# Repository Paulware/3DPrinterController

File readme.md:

3D Printer Controller

Parts
  $4 HBridge: 
  <br>
  [Get $4 HBridge on ebay](http://www.ebay.com/itm/L298N-DC-Stepper-Motor-Dual-H-Bridge-Drive-Controller-Board-Module-for-Arduino-/380520063503?)
  
Online videos:
  [Prototype](http://www.youtube.com/watch?v=m45CU5rBINc)    

Project Status
* Initial Creation 2/18/2013
* Ordered Updated board from Iteadstudio 2/22/2013
  
Questions/Comments
  paulware@hotmail.com
  
Help with projects
  [I help on Fiverr](http://fiverr.com/paulware/help-with-your-arduino-project)

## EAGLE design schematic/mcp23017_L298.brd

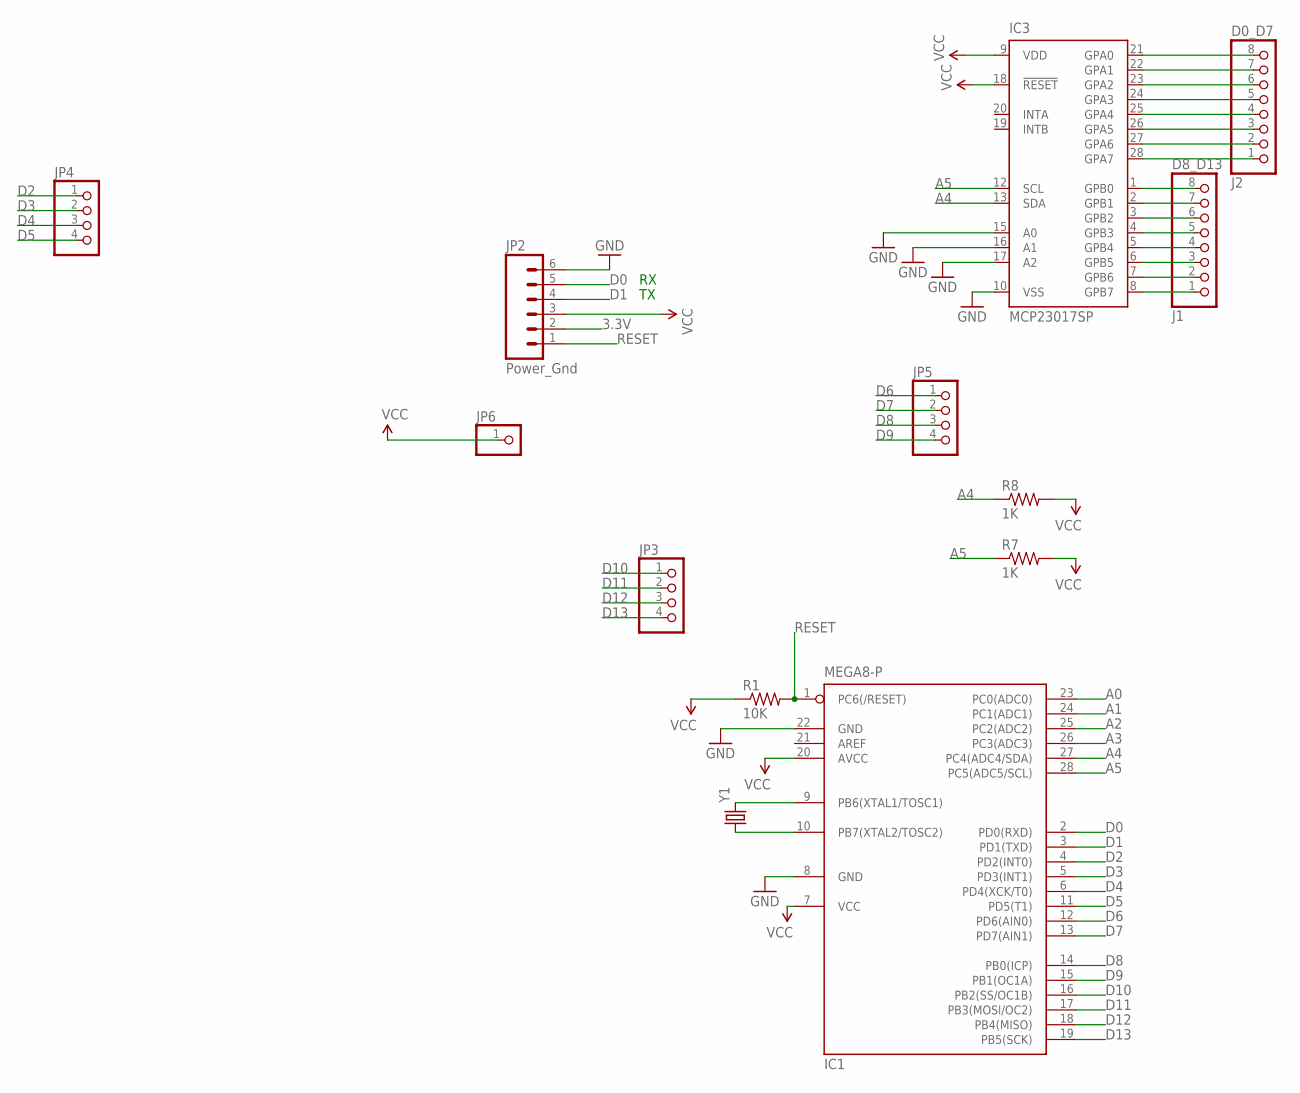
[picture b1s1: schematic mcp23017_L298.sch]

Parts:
IC1: MEGA8-P; DIL28-3
IC3: MCP23017SP; DIL28-3
J1: D8_D13; 1X08
J2: D0_D7; 1X08
JP2: Power_Gnd; 1X06
JP3, JP4, JP5: PINHD-1X4; 1X04
JP6: PINHD-1X1; 1X01
R1: 10K; 0207/10
R7, R8: 1K; 0207/10
Y1: CRYSTALHC49US; HC49US

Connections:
3.3V: JP2.2
A0: IC1.23 (PC0(ADC0))
A1: IC1.24 (PC1(ADC1))
A2: IC1.25 (PC2(ADC2))
A3: IC1.26 (PC3(ADC3))
A4: IC1.27 (PC4(ADC4/SDA)), IC3.13 (SDA), R8.1
A5: IC1.28 (PC5(ADC5/SCL)), IC3.12 (SCL), R7.1
D0: IC1.2 (PD0(RXD)), JP2.5
D1: IC1.3 (PD1(TXD)), JP2.4
D2: IC1.4 (PD2(INT0)), JP4.1
D3: IC1.5 (PD3(INT1)), JP4.2
D4: IC1.6 (PD4(XCK/T0)), JP4.3
D5: IC1.11 (PD5(T1)), JP4.4
D6: IC1.12 (PD6(AIN0)), JP5.1
D7: IC1.13 (PD7(AIN1)), JP5.2
D8: IC1.14 (PB0(ICP)), JP5.3
D9: IC1.15 (PB1(OC1A)), JP5.4
D10: IC1.16 (PB2(SS/OC1B)), JP3.1
D11: IC1.17 (PB3(MOSI/OC2)), JP3.2
D12: IC1.18 (PB4(MISO)), JP3.3
D13: IC1.19 (PB5(SCK)), JP3.4
GND: IC1.8 (GND), IC1.22 (GND), IC3.10 (VSS), IC3.15 (A0), IC3.16 (A1), IC3.17 (A2), JP2.6
unnamed: IC3.8 (GPB7), J1.1
unnamed: IC3.7 (GPB6), J1.2
unnamed: IC3.6 (GPB5), J1.3
unnamed: IC3.5 (GPB4), J1.4
unnamed: IC3.4 (GPB3), J1.5
unnamed: IC3.3 (GPB2), J1.6
unnamed: IC3.2 (GPB1), J1.7
unnamed: IC3.1 (GPB0), J1.8
unnamed: IC3.28 (GPA7), J2.1
unnamed: IC1.9 (PB6(XTAL1/TOSC1)), Y1.2
unnamed: IC1.10 (PB7(XTAL2/TOSC2)), Y1.1
unnamed: IC3.27 (GPA6), J2.2
unnamed: IC3.26 (GPA5), J2.3
unnamed: IC3.25 (GPA4), J2.4
unnamed: IC3.24 (GPA3), J2.5
unnamed: IC3.23 (GPA2), J2.6
unnamed: IC3.22 (GPA1), J2.7
unnamed: IC3.21 (GPA0), J2.8
RESET: IC1.1 (PC6(/RESET)), JP2.1, R1.2
VCC: IC1.7 (VCC), IC1.20 (AVCC), IC3.9 (VDD), IC3.18 (!RESET), JP2.3, JP6.1, R1.1, R7.2, R8.2

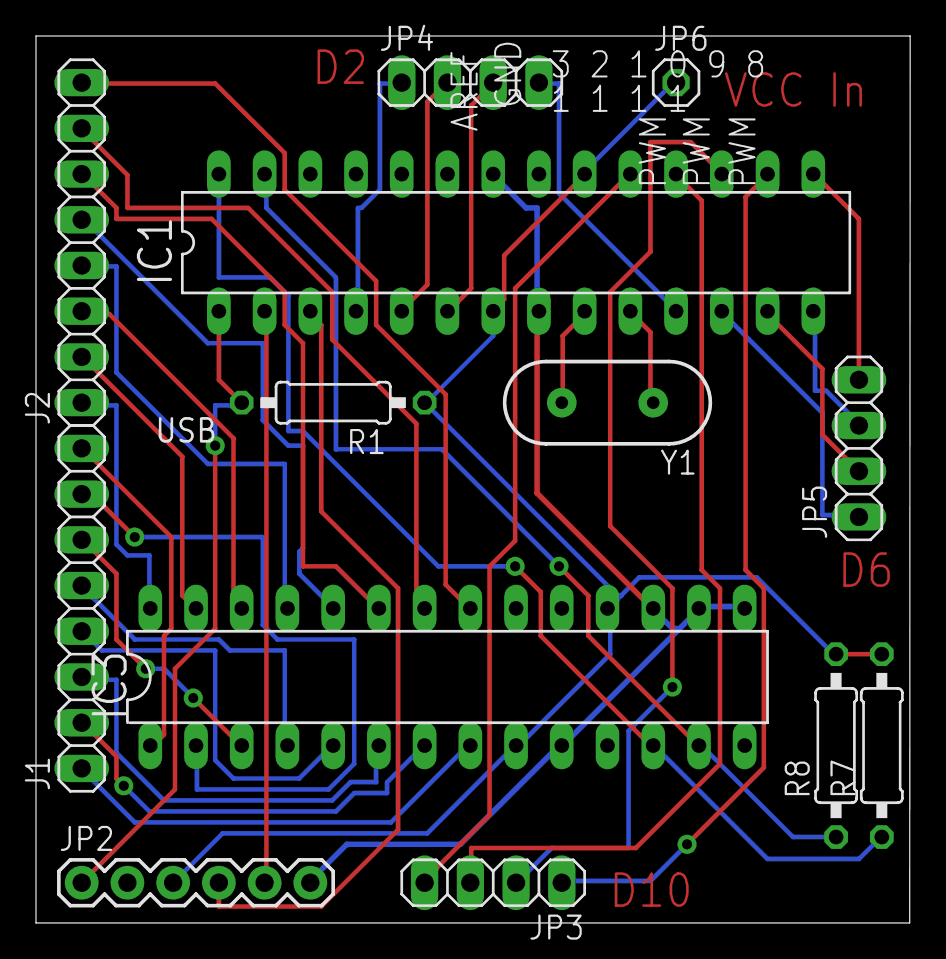
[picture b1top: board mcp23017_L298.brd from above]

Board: 2 copper layers, 48.6 x 49.3 mm, 13 parts (0 on the bottom side), 37 nets.

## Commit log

2013-02-21 v0.01
    Initial Creation
2013-02-21 v0.02
    Modified readme.md
2013-02-21 v0.03
    Modified readme.md
2013-02-21 v0.04
    Modified readme.md
2013-02-22 v0.05
    Ordered updated Schematic from Iteadstudio

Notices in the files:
parts and their libraries:
SparkFun-FreqCtrl: Licensing: CC v3.0 Share-Alike You are welcome to use this library for commercial purposes.
